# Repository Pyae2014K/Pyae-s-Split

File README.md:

# Pyae-s-Split

My split keyboard is a Corne like wired split keyboard.
It uses QMK firmware

It serves as a split keyboard that I can use to type on without getting sore quickly.

## Features:
- 42 Hot-swappable keys
- 3 Thumb keys on each side
- A TRRS cable for the two different parts to communicate
- [VIA](https://www.caniusevia.com/) support
- Doesn't need a case, only a PCB

## PCB:
My PC was made in Kicad

Schematic

PCB

I used [Joe Scotto's](https://www.youtube.com/@joe_scotto) footprints for most of my footprints.

## Firmware
This macropad uses [QMK](https://qmk.fm/) firmware.
- 42 keys
- Split functionality
- TRRS for intercommunication

## BOM:
Here is everything needed to make it.
| Qty | Part | Description | Price | Store |
|-----:|-----|-------------|-------|-------|
| 2 | Custom PCB | One left and one right board | $ 38.93 |  [JLCPCB](https://jlcpcb.com/) |
| 2 | Seeed XIAO RP2040 | Microcontroller | $ 5.00 | [HolyKeebs](https://holykeebs.com/products/xiao-rp2040?variant=49206715318562) |
| 45 | MX-Style Switches | Mechanical keyboard switch | $ 13.99 | [Amazon](https://www.amazon.com/gp/product/B0DP62N1RS/ref=ox_sc_act_title_1?smid=A1QXFO5SK4EVQJ&psc=1) |
| 50 | Kailh Hotswap Sockets | Hot-swap sockets | $ 6.25 | [HolyKeebs](https://holykeebs.com/products/kailh-mx-hotswap-sockets-10-pack?variant=45420412895522) |
| 40 | XDA Keycaps | XDA profile keycap | $ 14.00 | [HolyKeebs](https://holykeebs.com/products/xda-blank-keycaps?variant=48811660804386) |
| 2 | Homing XDA Keycaps | XDA profile keycap | $ 1.00 | [HolyKeebs](https://holykeebs.com/products/xda-blank-keycaps?variant=48811660837154) |
| 50 | 1N4148 Diodes | DO-35 through-hole diode | $ 0.43 | [LCSC](https://www.lcsc.com/product-detail/Switching-Diodes_luJing-1N4148_C49318123.html) |
| 2 | TRRS Port | Allows the halves to communicate | $ 0.13 | [LCSC](https://www.lcsc.com/product-detail/C22355837.html) |
| 1 | TRRS Male to Male Cable | Cable | $ 5.00 | [HolyKeebs](https://holykeebs.com/products/trrs-cable?variant=50301002875170) |

Total = 92.87

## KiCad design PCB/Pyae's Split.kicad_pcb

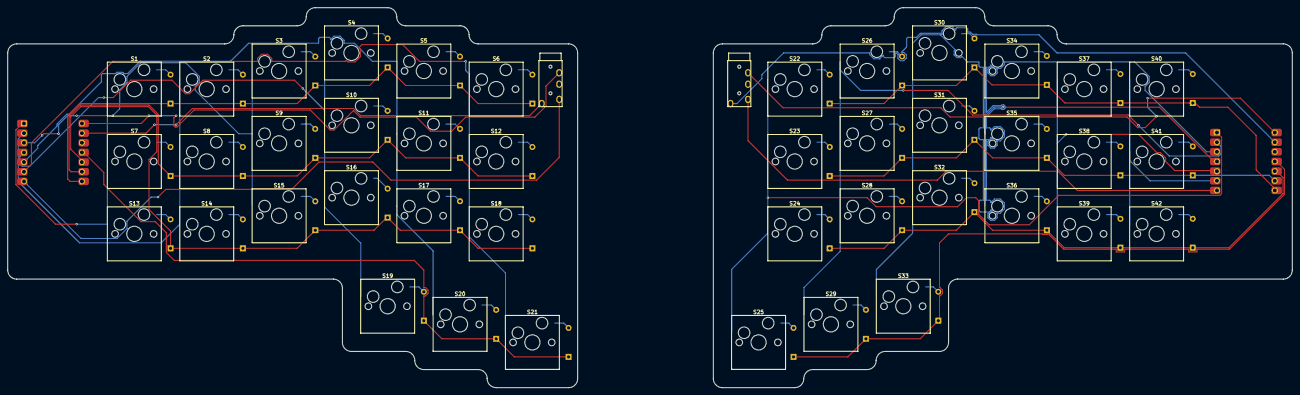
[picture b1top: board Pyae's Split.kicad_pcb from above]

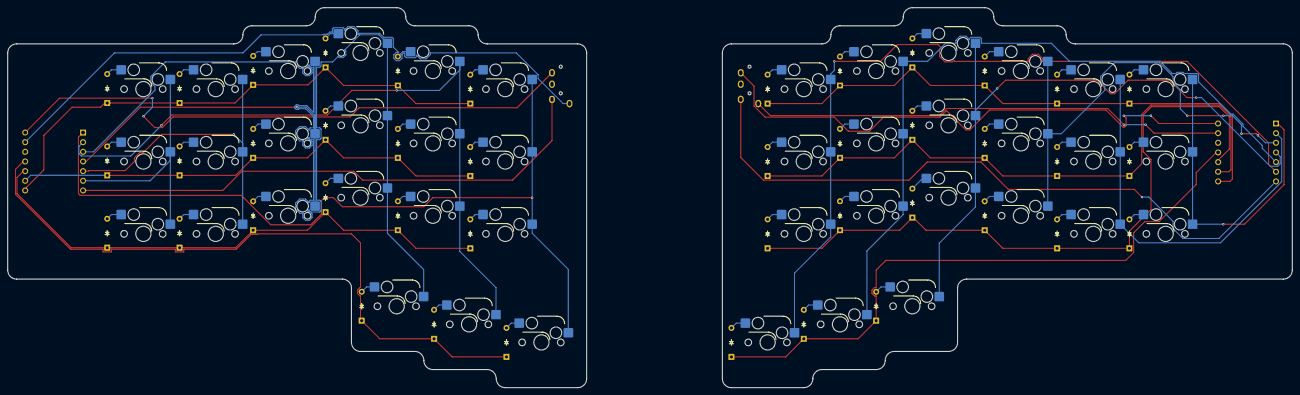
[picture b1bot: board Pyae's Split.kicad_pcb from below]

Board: 2 copper layers, 338.1 x 100.0 mm, 88 parts (42 on the bottom side), 66 nets.

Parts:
D1, D2, D3, D4, D5, D6, D7, D8, D9, D10, D11, D12, D13, D14, D15, D16, D17, D18, D19, D20, D21, D22, D23, D24, D25, D26, D27, D28, D29, D30, D31, D32, D33, D34, D35, D36, D37, D38, D39, D40, D41, D42: Diode_DO-35
S1, S2, S3, S4, S5, S6, S7, S8, S9, S10, S11, S12, S13, S14, S15, S16, S17, S18, S19, S20, S21, S22, S23, S24, S25, S26, S27, S28, S29, S30, S31, S32, S33, S34, S35, S36, S37, S38, S39, S40, S41, S42: Hotswap_MX_1.00u
U1, U2: MCU_Seeed_XIAO_RP2040; Seeed_XIAO_RP2040
U3, U4: TRRS; TRRS_PJ-320A

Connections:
+5V: U1.14 (5V), U2.14 (5V), U3.4 (RING2), U4.4 (RING2)
Col0: S1.1, S7.1, S13.1, U1.1 (PA02_A0_D0)
Col1: S2.1, S8.1, S14.1, U1.2 (PA4_A1_D1)
Col2: S3.1, S9.1, S15.1, U1.3 (PA10_A2_D2)
Col3: S4.1, S10.1, S16.1, S19.1, U1.4 (PA11_A3_D3)
Col4: S5.1, S11.1, S17.1, S20.1, U1.5 (PA8_A4_D4_SDA)
Col5: S6.1, S12.1, S18.1, S21.1, U1.6 (PA9_A5_D5_SCL)
Col6: S22.1, S23.1, S24.1, S25.1, U2.1 (PA02_A0_D0)
Col7: S26.1, S27.1, S28.1, S29.1, U2.2 (PA4_A1_D1)
Col8: S30.1, S31.1, S32.1, S33.1, U2.3 (PA10_A2_D2)
Col9: S34.1, S35.1, S36.1, U2.4 (PA11_A3_D3)
Col10: S37.1, S38.1, S39.1, U2.5 (PA8_A4_D4_SDA)
Col11: S40.1, S41.1, S42.1, U2.6 (PA9_A5_D5_SCL)
Data1: U1.7 (PB08_A6_D6_TX), U3.2 (TIP)
Data2: U2.7 (PB08_A6_D6_TX), U4.2 (TIP)
GND: U1.13 (GND), U2.13 (GND), U3.1 (SLEEVE), U4.1 (SLEEVE)
unnamed: D1.2 (A), S1.2
unnamed: D2.2 (A), S2.2
unnamed: D3.2 (A), S3.2
unnamed: D4.2 (A), S4.2
unnamed: D5.2 (A), S5.2
unnamed: D6.2 (A), S6.2
unnamed: D7.2 (A), S7.2
unnamed: D8.2 (A), S8.2
unnamed: D9.2 (A), S9.2
unnamed: D10.2 (A), S10.2
unnamed: D11.2 (A), S11.2
unnamed: D12.2 (A), S12.2
unnamed: D13.2 (A), S13.2
unnamed: D14.2 (A), S14.2
unnamed: D15.2 (A), S15.2
unnamed: D16.2 (A), S16.2
unnamed: D17.2 (A), S17.2
unnamed: D18.2 (A), S18.2
unnamed: D19.2 (A), S19.2
unnamed: D20.2 (A), S20.2
unnamed: D21.2 (A), S21.2
unnamed: D22.2 (A), S22.2
unnamed: D23.2 (A), S23.2
unnamed: D24.2 (A), S24.2
unnamed: D25.2 (A), S25.2
unnamed: D26.2 (A), S26.2
unnamed: D27.2 (A), S27.2
unnamed: D28.2 (A), S28.2
unnamed: D29.2 (A), S29.2
unnamed: D30.2 (A), S30.2
unnamed: D31.2 (A), S31.2
unnamed: D32.2 (A), S32.2
unnamed: D33.2 (A), S33.2
unnamed: D34.2 (A), S34.2
unnamed: D35.2 (A), S35.2
unnamed: D36.2 (A), S36.2
unnamed: D37.2 (A), S37.2
unnamed: D38.2 (A), S38.2
unnamed: D39.2 (A), S39.2
unnamed: D40.2 (A), S40.2
unnamed: D41.2 (A), S41.2
unnamed: D42.2 (A), S42.2
Row0: D1.1 (K), D2.1 (K), D3.1 (K), D4.1 (K), D5.1 (K), D6.1 (K), U1.8 (PB09_A7_D7_RX)
Row1: D7.1 (K), D8.1 (K), D9.1 (K), D10.1 (K), D11.1 (K), D12.1 (K), U1.9 (PA7_A8_D8_SCK)
Row2: D13.1 (K), D14.1 (K), D15.1 (K), D16.1 (K), D17.1 (K), D18.1 (K), U1.10 (PA5_A9_D9_MISO)
Row3: D19.1 (K), D20.1 (K), D21.1 (K), U1.11 (PA6_A10_D10_MOSI)
Row4: D22.1 (K), D26.1 (K), D30.1 (K), D34.1 (K), D37.1 (K), D40.1 (K), U2.8 (PB09_A7_D7_RX)
Row5: D23.1 (K), D27.1 (K), D31.1 (K), D35.1 (K), D38.1 (K), D41.1 (K), U2.9 (PA7_A8_D8_SCK)
Row6: D24.1 (K), D28.1 (K), D32.1 (K), D36.1 (K), D39.1 (K), D42.1 (K), U2.10 (PA5_A9_D9_MISO)
Row7: D25.1 (K), D29.1 (K), D33.1 (K), U2.11 (PA6_A10_D10_MOSI)

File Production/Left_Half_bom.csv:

Designator,Footprint,Quantity,Value,LCSC Part #
"D1, D10, D11, D12, D13, D14, D15, D16, D17, D18, D19, D2, D20, D21, D3, D4, D5, D6, D7, D8, D9",Diode_DO-35,21,~,
"S1, S10, S11, S12, S13, S14, S15, S16, S17, S18, S19, S2, S20, S21, S3, S4, S5, S6, S7, S8, S9",Hotswap_MX_1.00u,21,~,
U1,Seeed_XIAO_RP2040,1,MCU_Seeed_XIAO_RP2040,
U3,TRRS_PJ-320A,1,TRRS,
